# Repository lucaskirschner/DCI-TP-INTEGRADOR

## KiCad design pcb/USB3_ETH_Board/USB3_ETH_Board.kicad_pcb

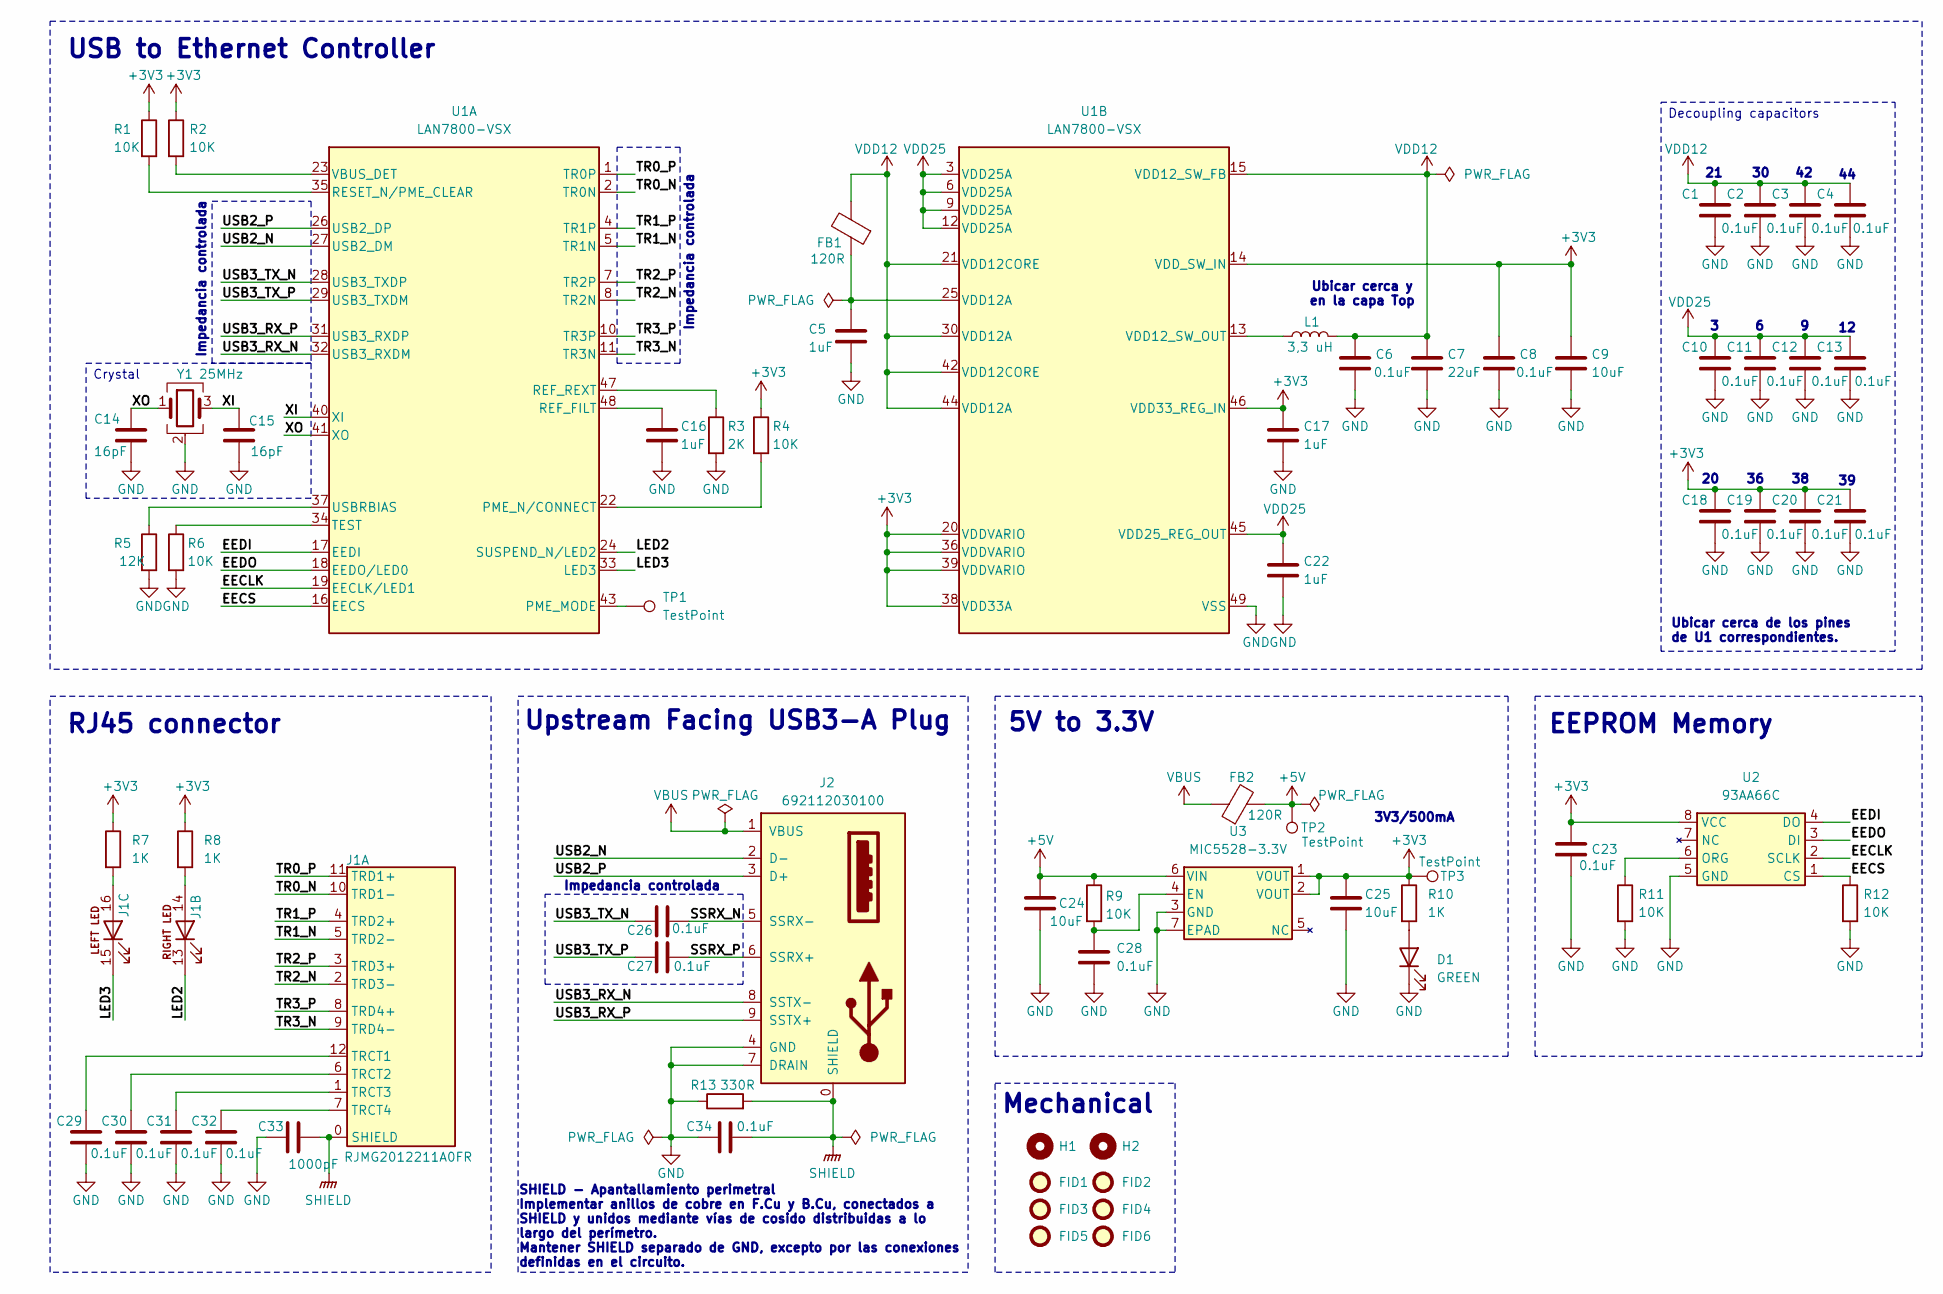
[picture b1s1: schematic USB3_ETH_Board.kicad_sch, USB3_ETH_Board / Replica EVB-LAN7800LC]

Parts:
C1, C2, C3, C4, C6, C8, C10, C11, C12, C13, C18, C19, C20, C21, C23, C26, C27, C28, C29, C30, C31, C32, C34: 0.1uF; C_0805_2012Metric; MPN GCM21BR72A104KA37L; Digikey Part # 490-4789-2-ND
C5, C16, C17, C22: 1uF; C_0805_2012Metric; MPN GCM21BR71C105KA58L; Digikey Part # 490-14437-2-ND
C7: 22uF; C_0805_2012Metric; MPN GRM219R60J226MEA0D; Digikey Part # 490-14463-2-ND
C9, C24, C25: 10uF; C_0805_2012Metric; MPN GRM21BC81E106KE51L; Digikey Part # 490-10502-2-ND
C14, C15: 16pF; C_0805_2012Metric; MPN GQM2195C2A160JB01D; Digikey Part # GQM2195C2A160JB01D-ND
C33: 1000pF; C_1812_4532Metric; MPN GR443QR73D102KW01L; Digikey Part # 490-12531-2-ND
D1: GREEN; LED_0805_2012Metric; MPN LTST-C171GKT; Digikey Part # 160-1423-2-ND
FB1, FB2: 120R; L_0805_2012Metric; MPN BLM21BB121SN1D; Digikey Part # 490-1042-2-ND
FID1, FID2, FID3, FID4, FID5, FID6: Fiducial; Fiducial_1mm_Mask2mm
H1, H2: MountingHole; MountingHole_2.5mm
J1: RJMG2012211A0FR; MPN RJMG2012211A0FR; Digikey Part # RJMG2012211A0FR-ND
J2: 692112030100; MPN 692112030100; Digikey Part # 732-3157-ND
L1: 3,3 uH; VLF302515MT-3R3M; MPN VLF302515MT-3R3M; Digikey Part # 445-9631-2-ND
R1, R2, R4, R6, R9, R11, R12: 10K; R_0805_2012Metric; MPN RC0805FR-0710KL; Digikey Part # 311-10.0KCRTR-ND
R3: 2K; R_0805_2012Metric; MPN RC0805FR-072KL; Digikey Part # 311-2.00KCRTR-ND
R5: 12K; R_0805_2012Metric; MPN RC0805FR-0712KL; Digikey Part # 311-12.0KCRTR-ND
R7, R8, R10: 1K; R_0805_2012Metric; MPN RC0805FR-071KL; Digikey Part # 311-1.00KCRTR-ND
R13: 330R; R_0805_2012Metric; MPN RC0805FR-07330RL; Digikey Part # 311-330CRTR-ND
TP1, TP2, TP3: TestPoint; 5003; MPN 5003; Digikey Part # 36-5003-ND
U1: LAN7800-VSX; MPN LAN7800/VSX; Digikey Part # LAN7800/VSX-ND
U2: 93AA66C; SOIC-8_3.9x4.9mm_P1.27mm; MPN 93AA66C-I/SN; Digikey Part # 93AA66C-I/SN-ND
U3: MIC5528-3.3V; MIC5528-3.3YMT-TR; MPN MIC5528-3.3YMT-TR; Digikey Part # 576-4766-2-ND
Y1: 25MHz; Crystal_SMD_3225-4Pin_3.2x2.5mm; MPN ABM8G-25.000MHZ-B4Y-T; Digikey Part # 535-10297-2-ND

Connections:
+3V3: C8.1, C9.1, C17.1, C18.1, C19.1, C20.1, C21.1, C23.1, C25.1, R1.1, R2.1, R4.1, R7.1, R8.1, R10.1, TP3.1 (1_1), U1.14 (VDD_SW_IN), U1.20 (VDDVARIO), U1.36 (VDDVARIO), U1.38 (VDD33A), U1.39 (VDDVARIO), U1.46 (VDD33_REG_IN), U2.8 (VCC), U3.1 (VOUT), U3.2 (VOUT)
+5V: C24.1, FB2.2, R9.1, TP2.1 (1_1), U3.6 (VIN)
/EECLK: U1.19 (EECLK/LED1), U2.2 (SCLK)
/EECS: R12.1, U1.16 (EECS), U2.1 (CS)
/EEDI: U1.17 (EEDI), U2.4 (DO)
/EEDO: U1.18 (EEDO/LED0), U2.3 (DI)
/LED2: J1.13, U1.24 (SUSPEND_N/LED2)
/LED3: J1.15, U1.33 (LED3)
/SSRX_N: C26.1, J2.5 (SSRX-)
/SSRX_P: C27.1, J2.6 (SSRX+)
/TR0_N: J1.10 (TRD1-), U1.2 (TR0N)
/TR0_P: J1.11 (TRD1+), U1.1 (TR0P)
/TR1_N: J1.5 (TRD2-), U1.5 (TR1N)
/TR1_P: J1.4 (TRD2+), U1.4 (TR1P)
/TR2_N: J1.2 (TRD3-), U1.8 (TR2N)
/TR2_P: J1.3 (TRD3+), U1.7 (TR2P)
/TR3_N: J1.9 (TRD4-), U1.11 (TR3N)
/TR3_P: J1.8 (TRD4+), U1.10 (TR3P)
/USB2_N: J2.2 (D-), U1.27 (USB2_DM)
/USB2_P: J2.3 (D+), U1.26 (USB2_DP)
/USB3_RX_N: J2.8 (SSTX-), U1.32 (USB3_RXDM)
/USB3_RX_P: J2.9 (SSTX+), U1.31 (USB3_RXDP)
/USB3_TX_N: C26.2, U1.28 (USB3_TXDP)
/USB3_TX_P: C27.2, U1.29 (USB3_TXDM)
/XI: C15.1, U1.40 (XI), Y1.3
/XO: C14.1, U1.41 (XO), Y1.1
GND: C1.2, C2.2, C3.2, C4.2, C5.2, C6.2, C7.2, C8.2, C9.2, C10.2, C11.2, C12.2, C13.2, C14.2, C15.2, C16.2, C17.2, C18.2, C19.2, C20.2, C21.2, C22.2, C23.2, C24.2, C25.2, C28.2, C29.2, C30.2, C31.2, C32.2, C33.2, C34.2, D1.1 (K), J2.4 (GND), J2.7 (DRAIN), R3.2, R5.2, R6.2, R11.2, R12.2, R13.1, U1.49 (VSS), U2.5 (GND), U3.3 (GND), U3.7 (EPAD), Y1.2 (G), Y1.4 (G)
unnamed: C5.1, FB1.1, U1.25 (VDD12A)
unnamed: D1.2 (A), R10.2
unnamed: J1.14, R8.2
unnamed: J1.16, R7.2
unnamed: C29.1, J1.12 (TRCT1)
unnamed: C30.1, J1.6 (TRCT2)
unnamed: C31.1, J1.1 (TRCT3)
unnamed: C32.1, J1.7 (TRCT4)
unnamed: TP1.1 (1_1), U1.43 (PME_MODE)
unnamed: R4.2, U1.22 (PME_N/CONNECT)
unnamed: C16.1, U1.48 (REF_FILT)
unnamed: R3.1, U1.47 (REF_REXT)
unnamed: R1.2, U1.35 (RESET_N/PME_CLEAR)
unnamed: R6.1, U1.34 (TEST)
unnamed: R5.1, U1.37 (USBRBIAS)
unnamed: R2.2, U1.23 (VBUS_DET)
unnamed: L1.1, U1.13 (VDD12_SW_OUT)
unnamed: R11.1, U2.6 (ORG)
unnamed: C28.1, R9.2, U3.4 (EN)
SHIELD: C33.1, C34.1, J1.0 (SHIELD), J2.0 (SHIELD), R13.2
VBUS: FB2.1, J2.1 (VBUS)
VDD12: C1.1, C2.1, C3.1, C4.1, C6.1, C7.1, FB1.2, L1.2, U1.15 (VDD12_SW_FB), U1.21 (VDD12CORE), U1.30 (VDD12A), U1.42 (VDD12CORE), U1.44 (VDD12A)
VDD25: C10.1, C11.1, C12.1, C13.1, C22.1, U1.3 (VDD25A), U1.6 (VDD25A), U1.9 (VDD25A), U1.12 (VDD25A), U1.45 (VDD25_REG_OUT)

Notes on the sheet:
Decoupling capacitors
RJ45 connector
Ubicar cerca y en la capa Top
Upstream Facing USB3-A Plug
Impedancia controlada
EEPROM Memory
Crystal
5V to 3.3V
3V3/500mA
SHIELD - Apantallamiento perimetral Implementar anillos de cobre en F.Cu y B.Cu, conectados a SHIELD y unidos mediante vías de cosido distribuidas a lo largo del perímetro. Mantener SHIELD separado de GND, excepto por las conexiones definidas en el circuito.
USB to Ethernet Controller
Ubicar cerca de los pines de U1 correspondientes.
Mechanical

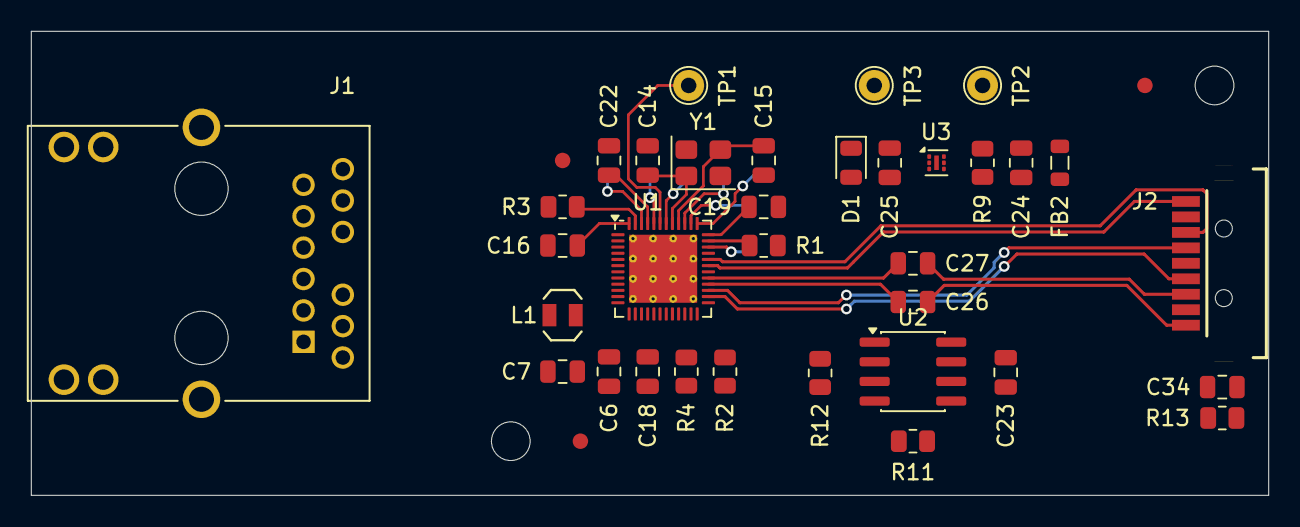
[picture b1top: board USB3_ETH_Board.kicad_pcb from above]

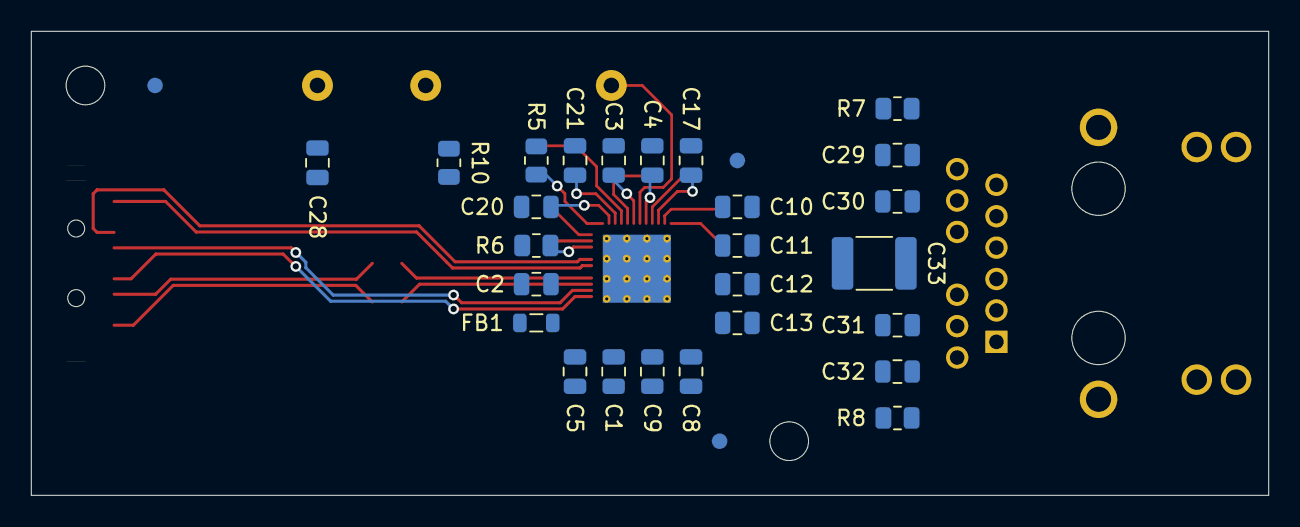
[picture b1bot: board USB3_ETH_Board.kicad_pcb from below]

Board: 4 copper layers, 80.0 x 30.0 mm, 68 parts (29 on the bottom side), 50 nets.

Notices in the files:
pcb/USB3_ETH_Board/USB3_ETH_Board.kicad_pcb:
License: CERN-OHL-S-2.0
